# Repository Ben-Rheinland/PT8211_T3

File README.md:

# PT8211_T3
This is an adapter board ("shield") for the Teensy 3.x by PJRC.<br>
It features the cheap two-channel DAC PT8211 by Princeton Technology and adds a power supply filter, an analog third order low pass filter and output buffering.
<br>
https://forum.pjrc.com/threads/29284-Dual-channel-16bit-dac-PT8211

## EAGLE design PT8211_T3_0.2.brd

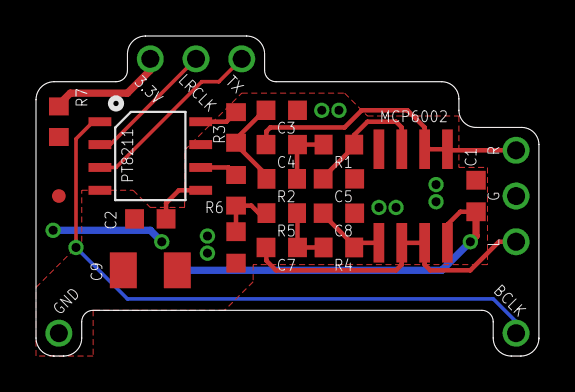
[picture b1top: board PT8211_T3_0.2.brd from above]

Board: 2 copper layers, 27.9 x 17.8 mm, 27 parts (0 on the bottom side), 16 nets.

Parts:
3.3V: SOLPAD1,0MM; SOLPAD1MM
BCLK: SOLPAD1,0MM; SOLPAD1MM
C1, C2: X7R-G0603 100N; C0603K
C3, C4, C6, C7: NPO-G0603 330P; C0603K
C5, C8: NPO-G0603 47P; C0603K
C9: X5R-G1206 100/6; C1206K
G: SOLPAD1,0MM; SOLPAD1MM
GND: SOLPAD1,0MM; SOLPAD1MM
L: SOLPAD1,0MM; SOLPAD1MM
LRCLK: SOLPAD1,0MM; SOLPAD1MM
MCP6002: MCP6002; SO08
R: SOLPAD1,0MM; SOLPAD1MM
R1, R4: SMD-0603 33K; R0603
R2, R5: SMD-0603 68K; R0603
R3, R6: SMD-0603 22K; R0603
R7: SMD-0603 10; R0603
TP1: TEST-POINT3; PAD.03X.03
TX: SOLPAD1,0MM; SOLPAD1MM
U1: PT8211; SOP8-6.0-4.9X3.9

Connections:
BCK: BCLK.P$1, U1.1
DIN: TX.P$1, U1.3
GND: C1.2, C2.2, C3.2, C5.1, C6.2, C8.1, C9.2, G.P$1, GND.P$1, MCP6002.4, U1.4
unnamed: C6.1, R5.1, R6.2
unnamed: C7.2, R4.1, R5.2
unnamed: C8.2, MCP6002.5, R4.2
unnamed: C3.1, R2.1, R3.2
unnamed: C4.2, R1.1, R2.2
unnamed: C5.2, MCP6002.3, R1.2
unnamed: 3.3V.P$1, R7.1
unnamed: R6.1, U1.6
unnamed: R3.1, U1.8
OUTL: C7.1, L.P$1, MCP6002.6, MCP6002.7
OUTR: C4.1, MCP6002.1, MCP6002.2, R.P$1
VDD: C1.1, C2.1, C9.1, MCP6002.8, R7.2, U1.5
WS: LRCLK.P$1, U1.2

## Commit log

2016-07-26 :tada: Added .gitattributes & .gitignore files
2016-07-26 First upload, V0.1
2016-07-26 Add documentation PDFs
2016-07-27 Change supply voltage filter, re-route power rail,
    Supply voltage filtering now is an RC-filter with 10 Ohms, 100µF instead
    of ferrite and 2x 100nF

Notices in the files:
parts and their libraries:
SparkFun: Licensing: CC v3.0 Share-Alike You are welcome to use this library for commercial purposes.
